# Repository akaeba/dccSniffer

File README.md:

# dccSniffer
Arduino based DCC Sniffer

## Gallery

## References
* [Arduino Nano: Pinout](https://iotspace.dev/arduino-nano-pinout/)
* [Github: DCCInspector-EX](https://github.com/DCC-EX/DCCInspector-EX)

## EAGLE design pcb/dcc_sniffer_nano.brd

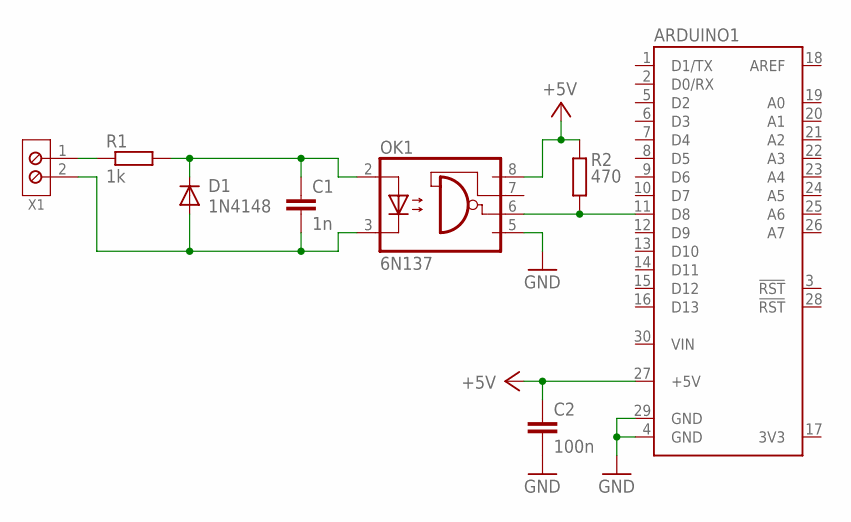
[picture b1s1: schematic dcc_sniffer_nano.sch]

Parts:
ARDUINO1: ARDUINO_NANO
C1: 1n; C025-025X050
C2: 100n; C025-025X050
D1: 1N4148; DO35_L10M0
OK1: 6N137; DIL08
R1: 1k; 0207/10
R2: 470; 0207/10
X1: RT034 Typ 086; RT03402T086

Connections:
+5V: ARDUINO1.27 (+5V), C2.1, OK1.8 (VCC), R2.2
GND: ARDUINO1.4 (GND), ARDUINO1.29 (GND), C2.2, OK1.5 (GND)
unnamed: C1.1, D1.C, OK1.2 (A), R1.2
unnamed: C1.2, D1.A, OK1.3 (C), X1.2
unnamed: ARDUINO1.11 (D8), OK1.6 (VO), R2.1
unnamed: R1.1, X1.1
VIN: ARDUINO1.30 (VIN)

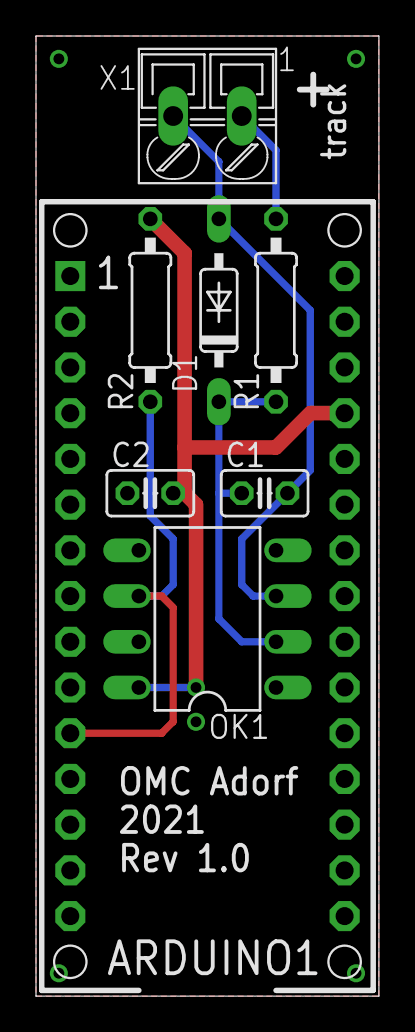
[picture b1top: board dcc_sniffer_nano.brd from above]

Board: 2 copper layers, 19.1 x 53.3 mm, 8 parts (0 on the bottom side), 6 nets.

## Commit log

2021-09-19 add AFE
2021-09-19 add DCC sniffing arduino FW
2021-09-19 add links
2021-09-19 BOM listing
2021-09-19 add Reichelt import list
2021-10-03 add Pics from HW
2021-10-03 change size
2021-10-03 size
2021-10-08 bugfix: assign to IRQ input pin
2021-10-08 add PDF schematic

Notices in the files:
parts and their libraries:
omcDiode: Copyright & License
This library is licensed under the General Public License, Version 3.
More Information about the General Public License is available at http://www.gnu.org/copyleft/gpl.html.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
omcConnector: This library is licensed under the General Public License, Version 2.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
